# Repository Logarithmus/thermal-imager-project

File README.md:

# thermal-imager-project
My university project for the 6th term

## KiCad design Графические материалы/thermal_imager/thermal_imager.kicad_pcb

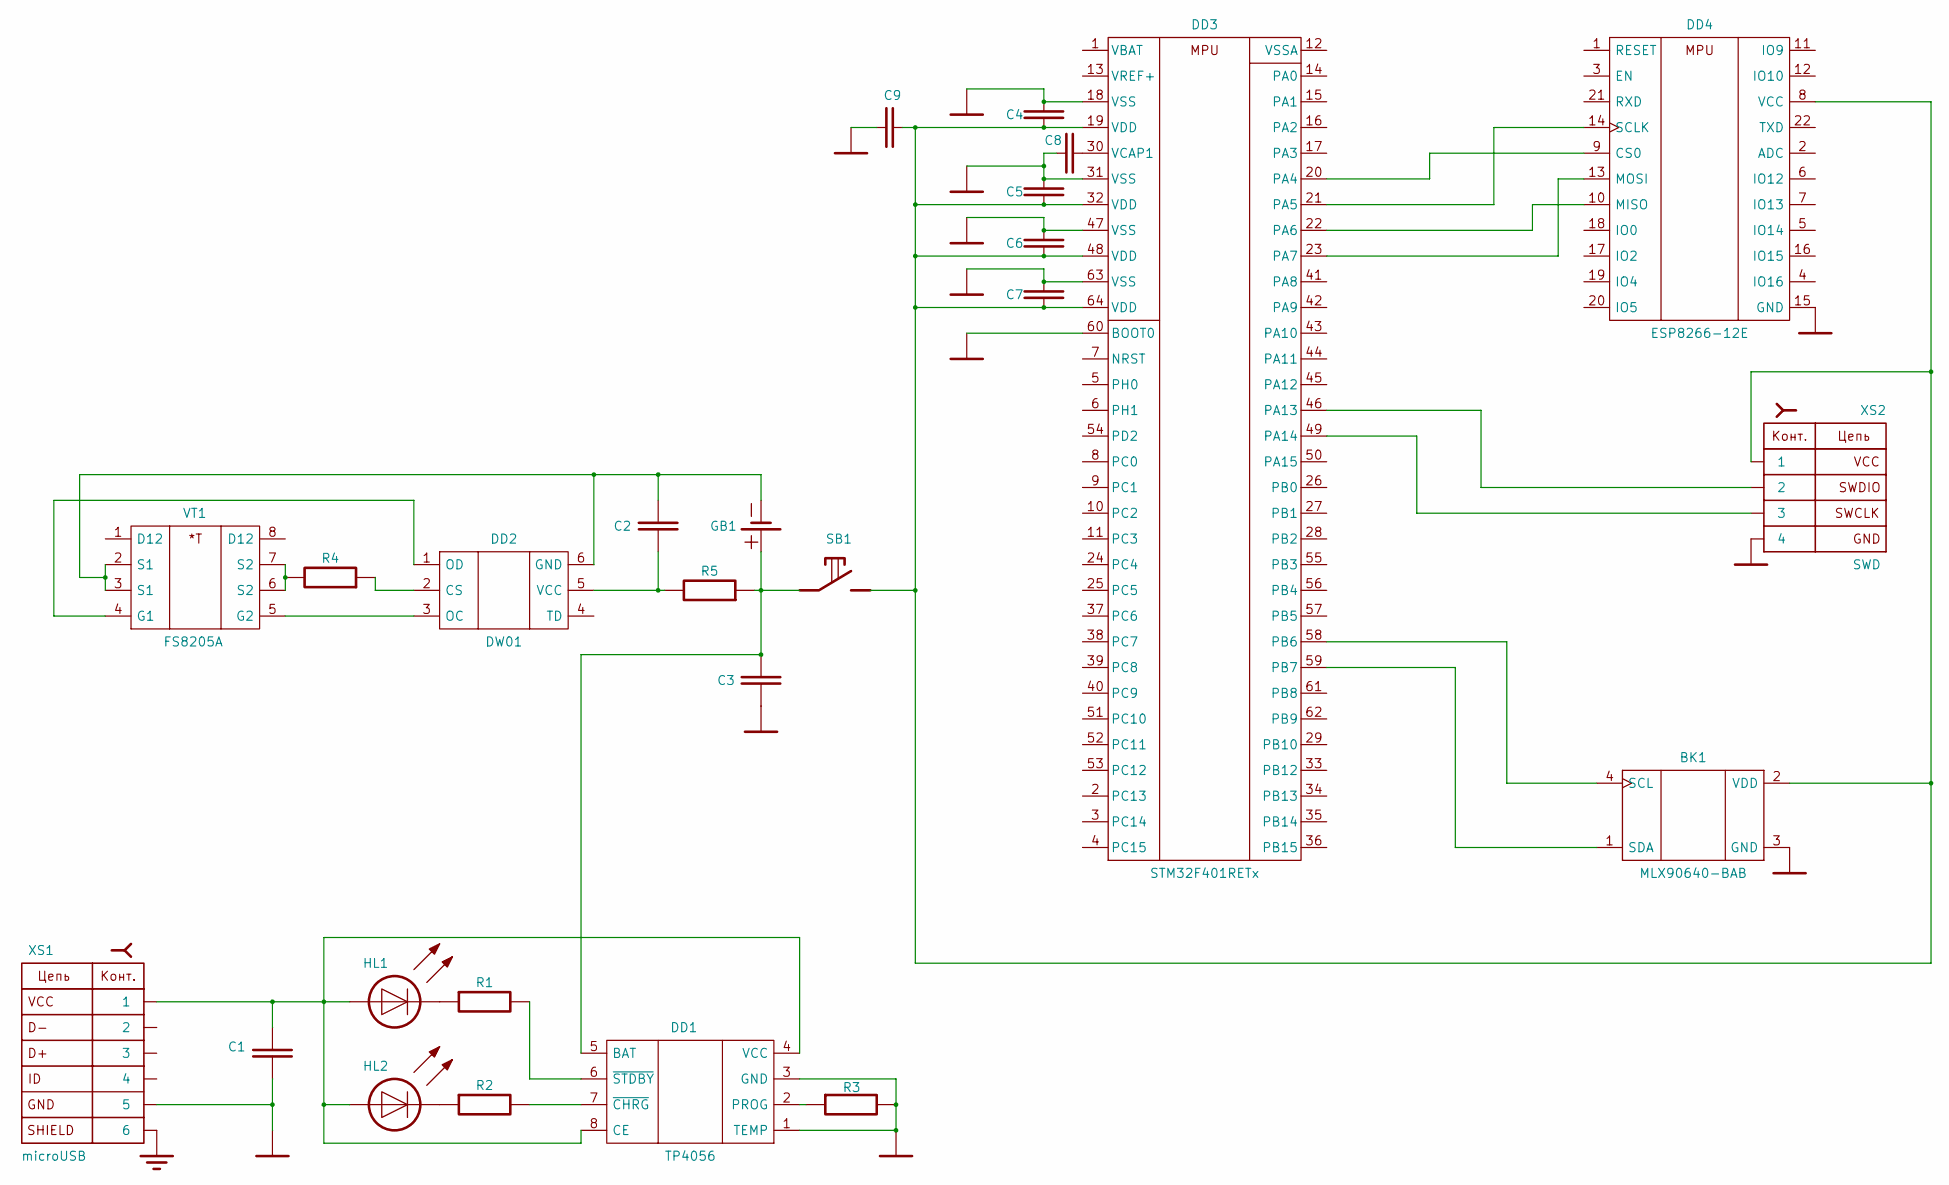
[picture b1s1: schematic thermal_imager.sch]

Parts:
BK1: MLX90640-BAB; TO292P945H1165-4
C1: 0,1uF; C_Disc_D3.0mm_W1.6mm_P2.50mm
C2: 0.1uF; C_Disc_D3.0mm_W1.6mm_P2.50mm
C3: 10uF; C_Radial_D4.0mm_H5.0mm_P1.50mm
C4, C5, C6, C7: 100nF; C_Disc_D3.0mm_W1.6mm_P2.50mm
C8: 2.2uF; C_Radial_D4.0mm_H5.0mm_P1.50mm
C9: 4.7uF; C_Radial_D4.0mm_H5.0mm_P1.50mm
DD1: TP4056; SOP-8
DD2: DW01; SOT23-6
DD3: STM32F401RETx; LQFP-64_10x10mm_P0.5mm
DD4: ESP8266-12E; ESP-12E
GB1: GB_BATTERY; TestPoint_2Pads_Pitch2.54mm_Drill0.8mm
HL1, HL2: HL_LED; LED_D3.0mm
R1, R2, R4: 1k; R_Axial_DIN0204_L3.6mm_D1.6mm_P5.08mm_Horizontal
R3: 10k; R_Axial_DIN0204_L3.6mm_D1.6mm_P5.08mm_Horizontal
R5: 100; R_Axial_DIN0204_L3.6mm_D1.6mm_P5.08mm_Horizontal
SB1: SB_ON; SW_DIP_SPSTx01_Slide_6.7x4.1mm_W7.62mm_P2.54mm_LowProfile
VT1: FS8205A; SOP65P640X120-8N
XS1: microUSB; USB_Micro-B_Molex-105133-0001
XS2: SWD

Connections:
GND: BK1.3 (GND), C1.1, C3.2, C4.1, C5.1, C6.1, C7.1, C8.1, C9.1, DD1.1 (TEMP), DD1.3 (GND), DD3.18 (VSS), DD3.31 (VSS), DD3.47 (VSS), DD3.60 (BOOT0), DD3.63 (VSS), DD4.15 (GND), R3.2, XS1.5, XS2.4
unnamed: BK1.1 (SDA), DD3.59 (PB7)
unnamed: BK1.2 (VDD), C4.2, C5.2, C6.2, C7.2, C9.2, DD3.19 (VDD), DD3.32 (VDD), DD3.48 (VDD), DD3.64 (VDD), DD4.8 (VCC), SB1.2, XS2.1
unnamed: BK1.4 (SCL), DD3.58 (PB6)
unnamed: C1.2, DD1.4 (VCC), DD1.8 (CE), HL1.2 (C), HL2.2 (C), XS1.1
unnamed: C2.1, DD2.5 (VCC), R5.2
unnamed: C2.2, DD2.6 (GND), GB1.2 (-), VT1.2 (S1), VT1.3 (S1)
unnamed: C3.1, DD1.5 (BAT), GB1.1 (+), R5.1, SB1.1
unnamed: C8.2, DD3.30 (VCAP1)
unnamed: DD1.2 (PROG), R3.1
unnamed: DD1.6 (~STDBY), R1.2
unnamed: DD1.7 (~CHRG), R2.2
unnamed: DD2.1 (OD), VT1.4 (G1)
unnamed: DD2.2 (CS), R4.1
unnamed: DD2.3 (OC), VT1.5 (G2)
unnamed: DD3.20 (PA4), DD4.9 (CS0)
unnamed: DD3.21 (PA5), DD4.14 (SCLK)
unnamed: DD3.22 (PA6), DD4.10 (MISO)
unnamed: DD3.23 (PA7), DD4.13 (MOSI)
unnamed: DD3.46 (PA13), XS2.2
unnamed: DD3.49 (PA14), XS2.3
unnamed: HL1.1 (A), R1.1
unnamed: HL2.1 (A), R2.1
unnamed: R4.2, VT1.6 (S2), VT1.7 (S2)

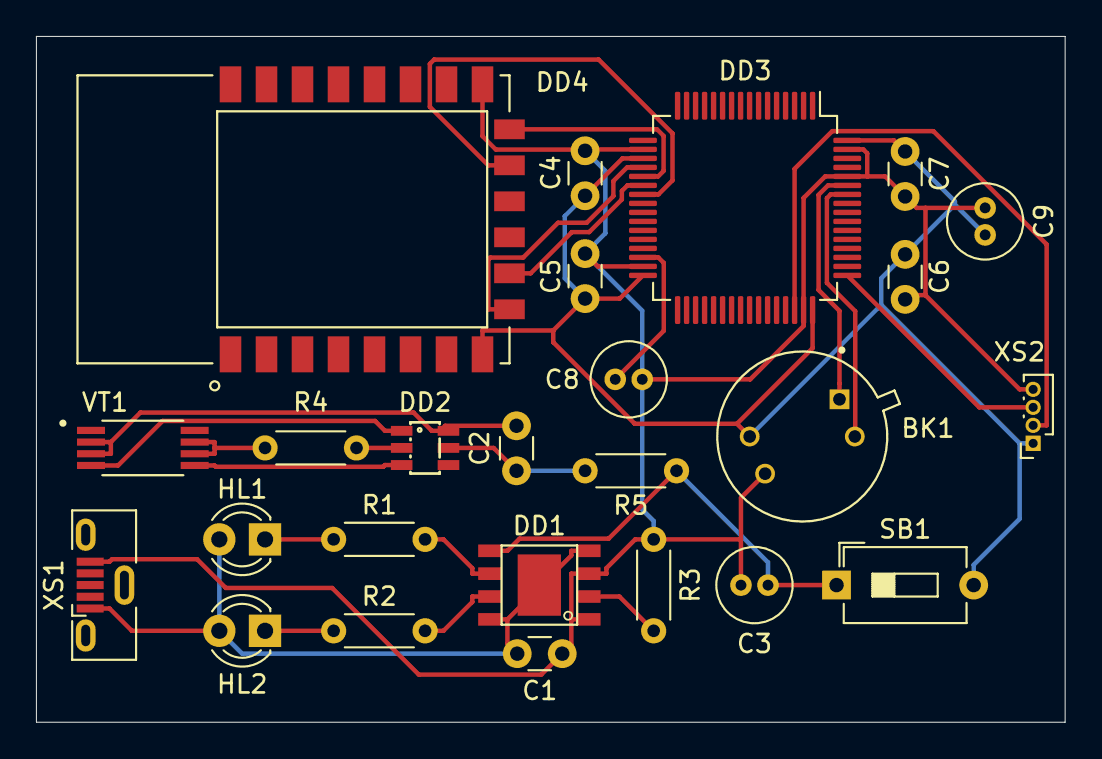
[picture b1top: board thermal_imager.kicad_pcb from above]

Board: 2 copper layers, 57.2 x 38.1 mm, 25 parts (0 on the bottom side), 24 nets.

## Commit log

2020-05-09 Начал пояснительную
2020-05-09 Создал структуру проекта
2020-05-09 Оформил стили и список (под)разделов
2020-05-12 10 hours left!
2020-05-12 Введение
2020-05-12 1.1 is complete
2020-05-14 Библиотека готова
2020-05-14 Исправил библиотеку
2020-05-16 ВРОДЕ СДЕЛАЛ СИМВОЛЫ ПО ГОСТУ
2020-05-18 Something
2020-05-19 Плакаты готовы
2020-05-19 Пояснительная теория почти готова
